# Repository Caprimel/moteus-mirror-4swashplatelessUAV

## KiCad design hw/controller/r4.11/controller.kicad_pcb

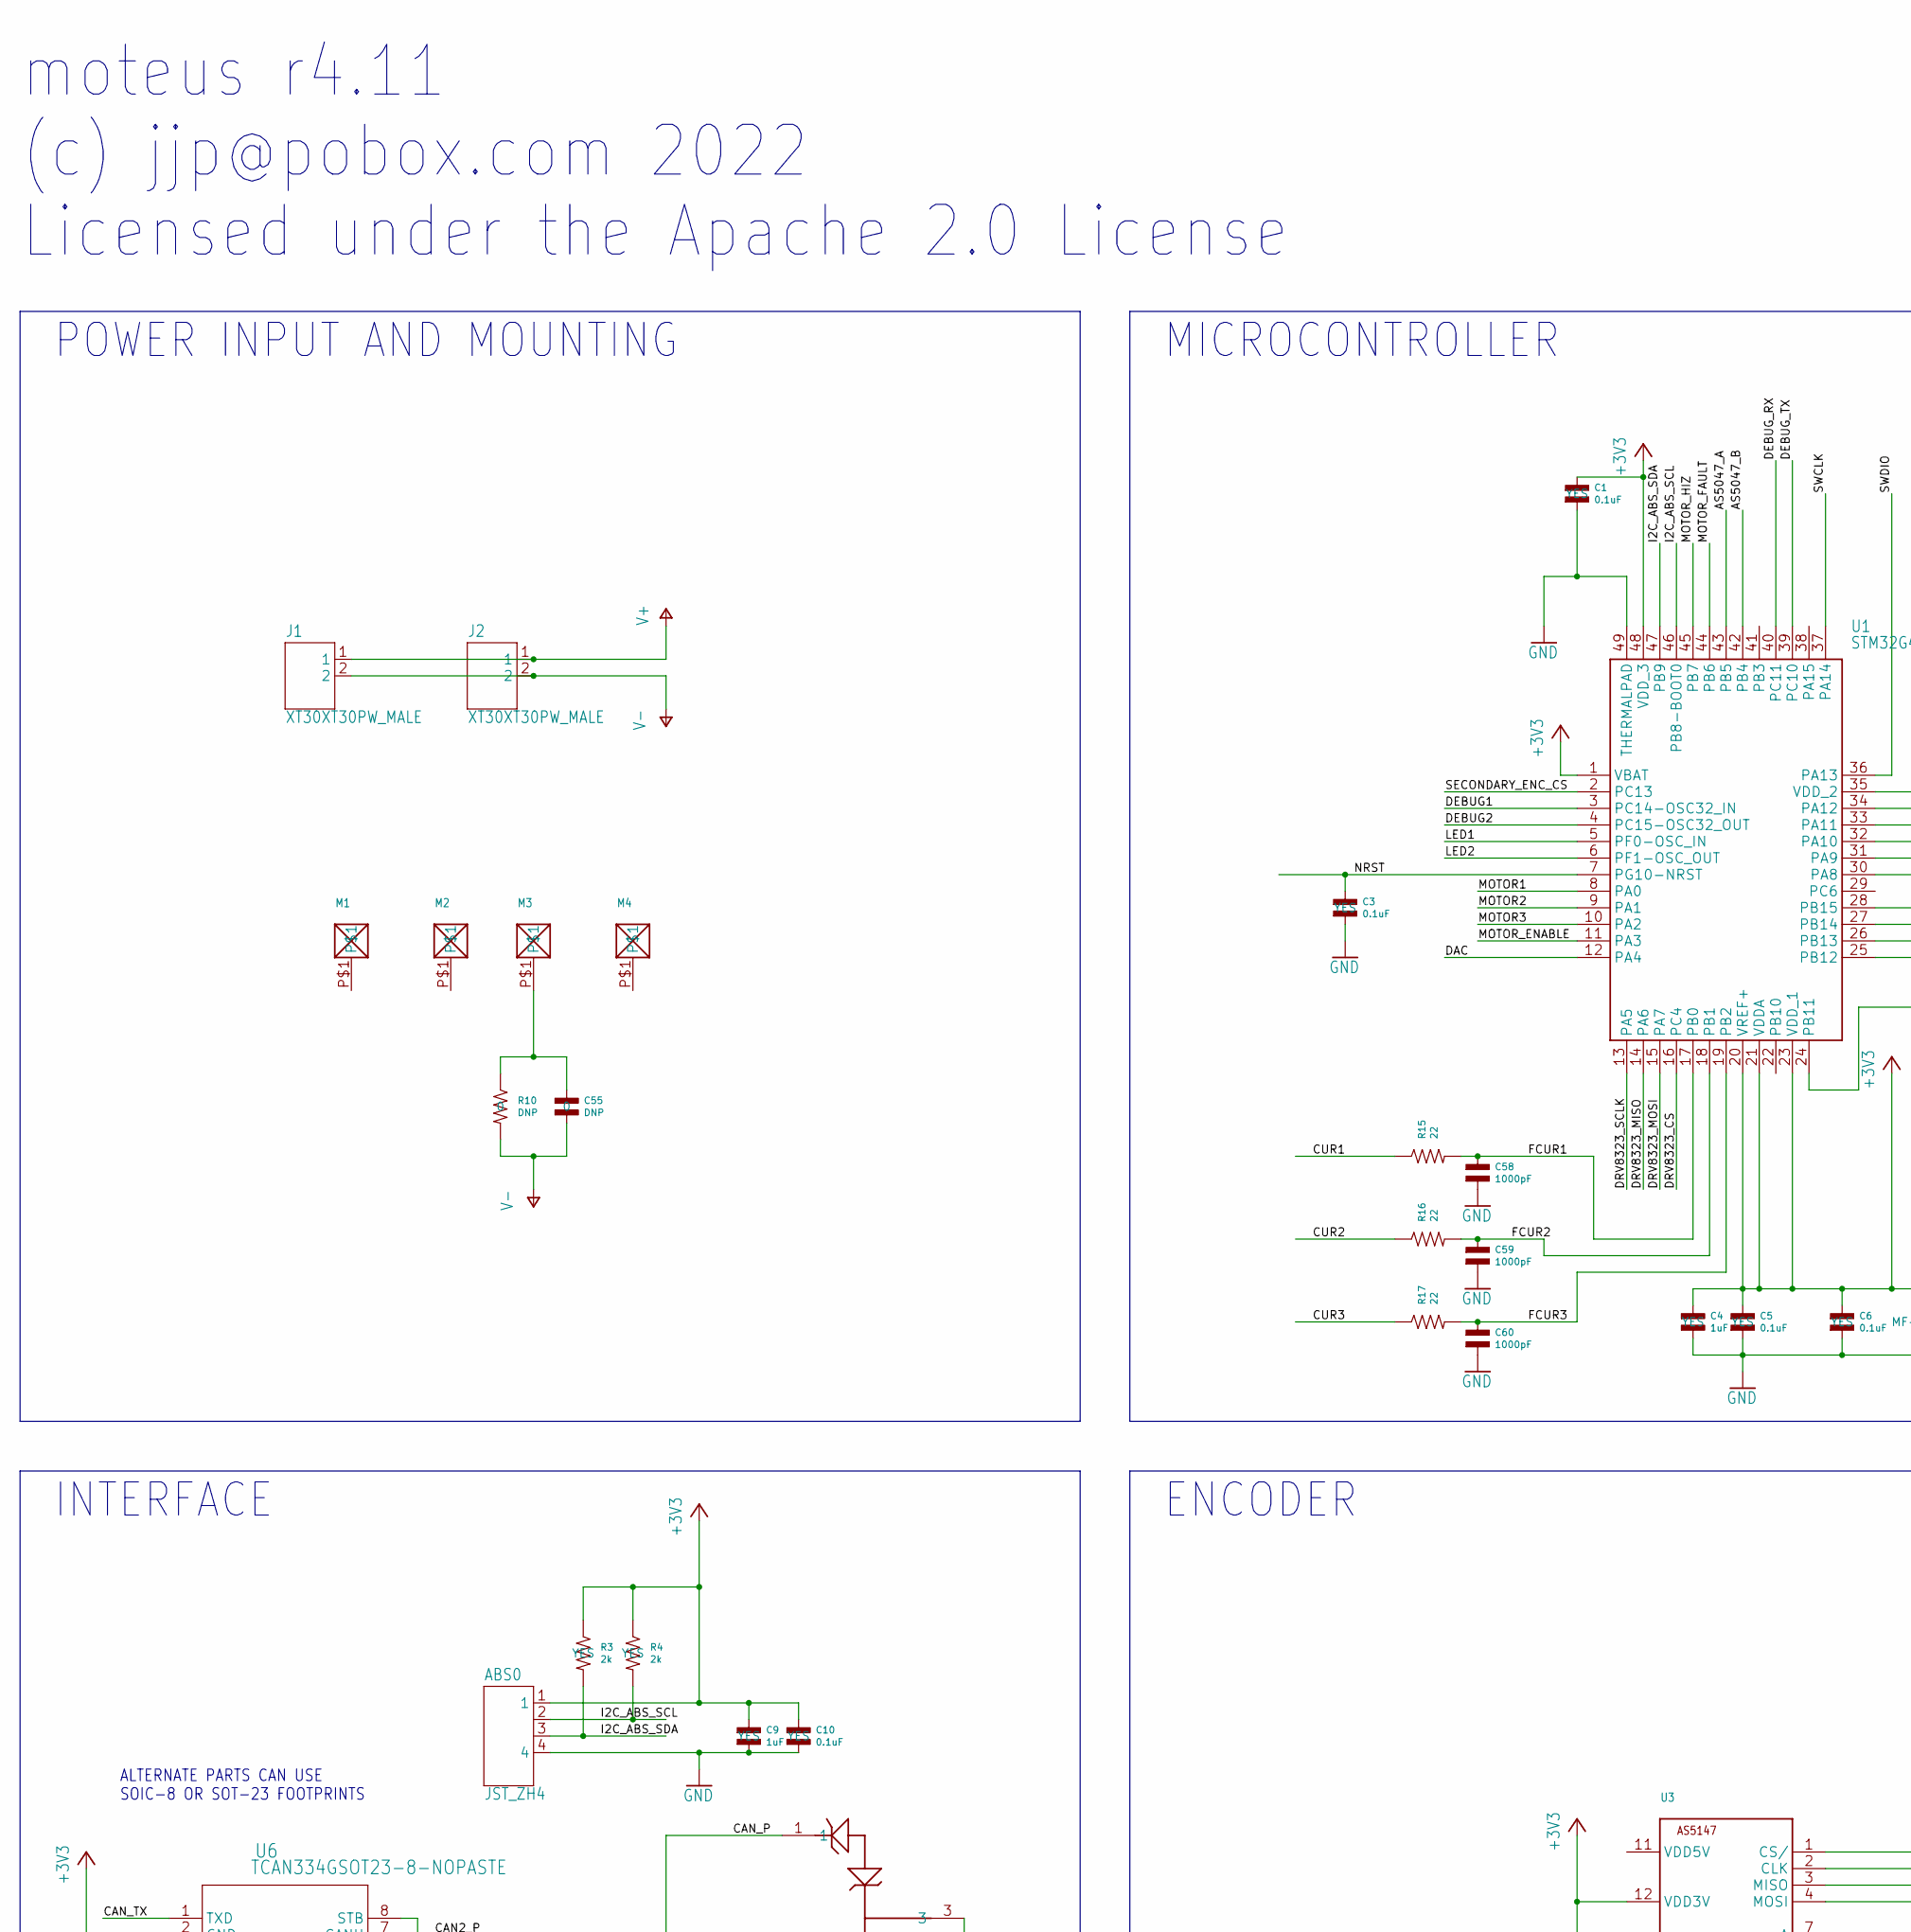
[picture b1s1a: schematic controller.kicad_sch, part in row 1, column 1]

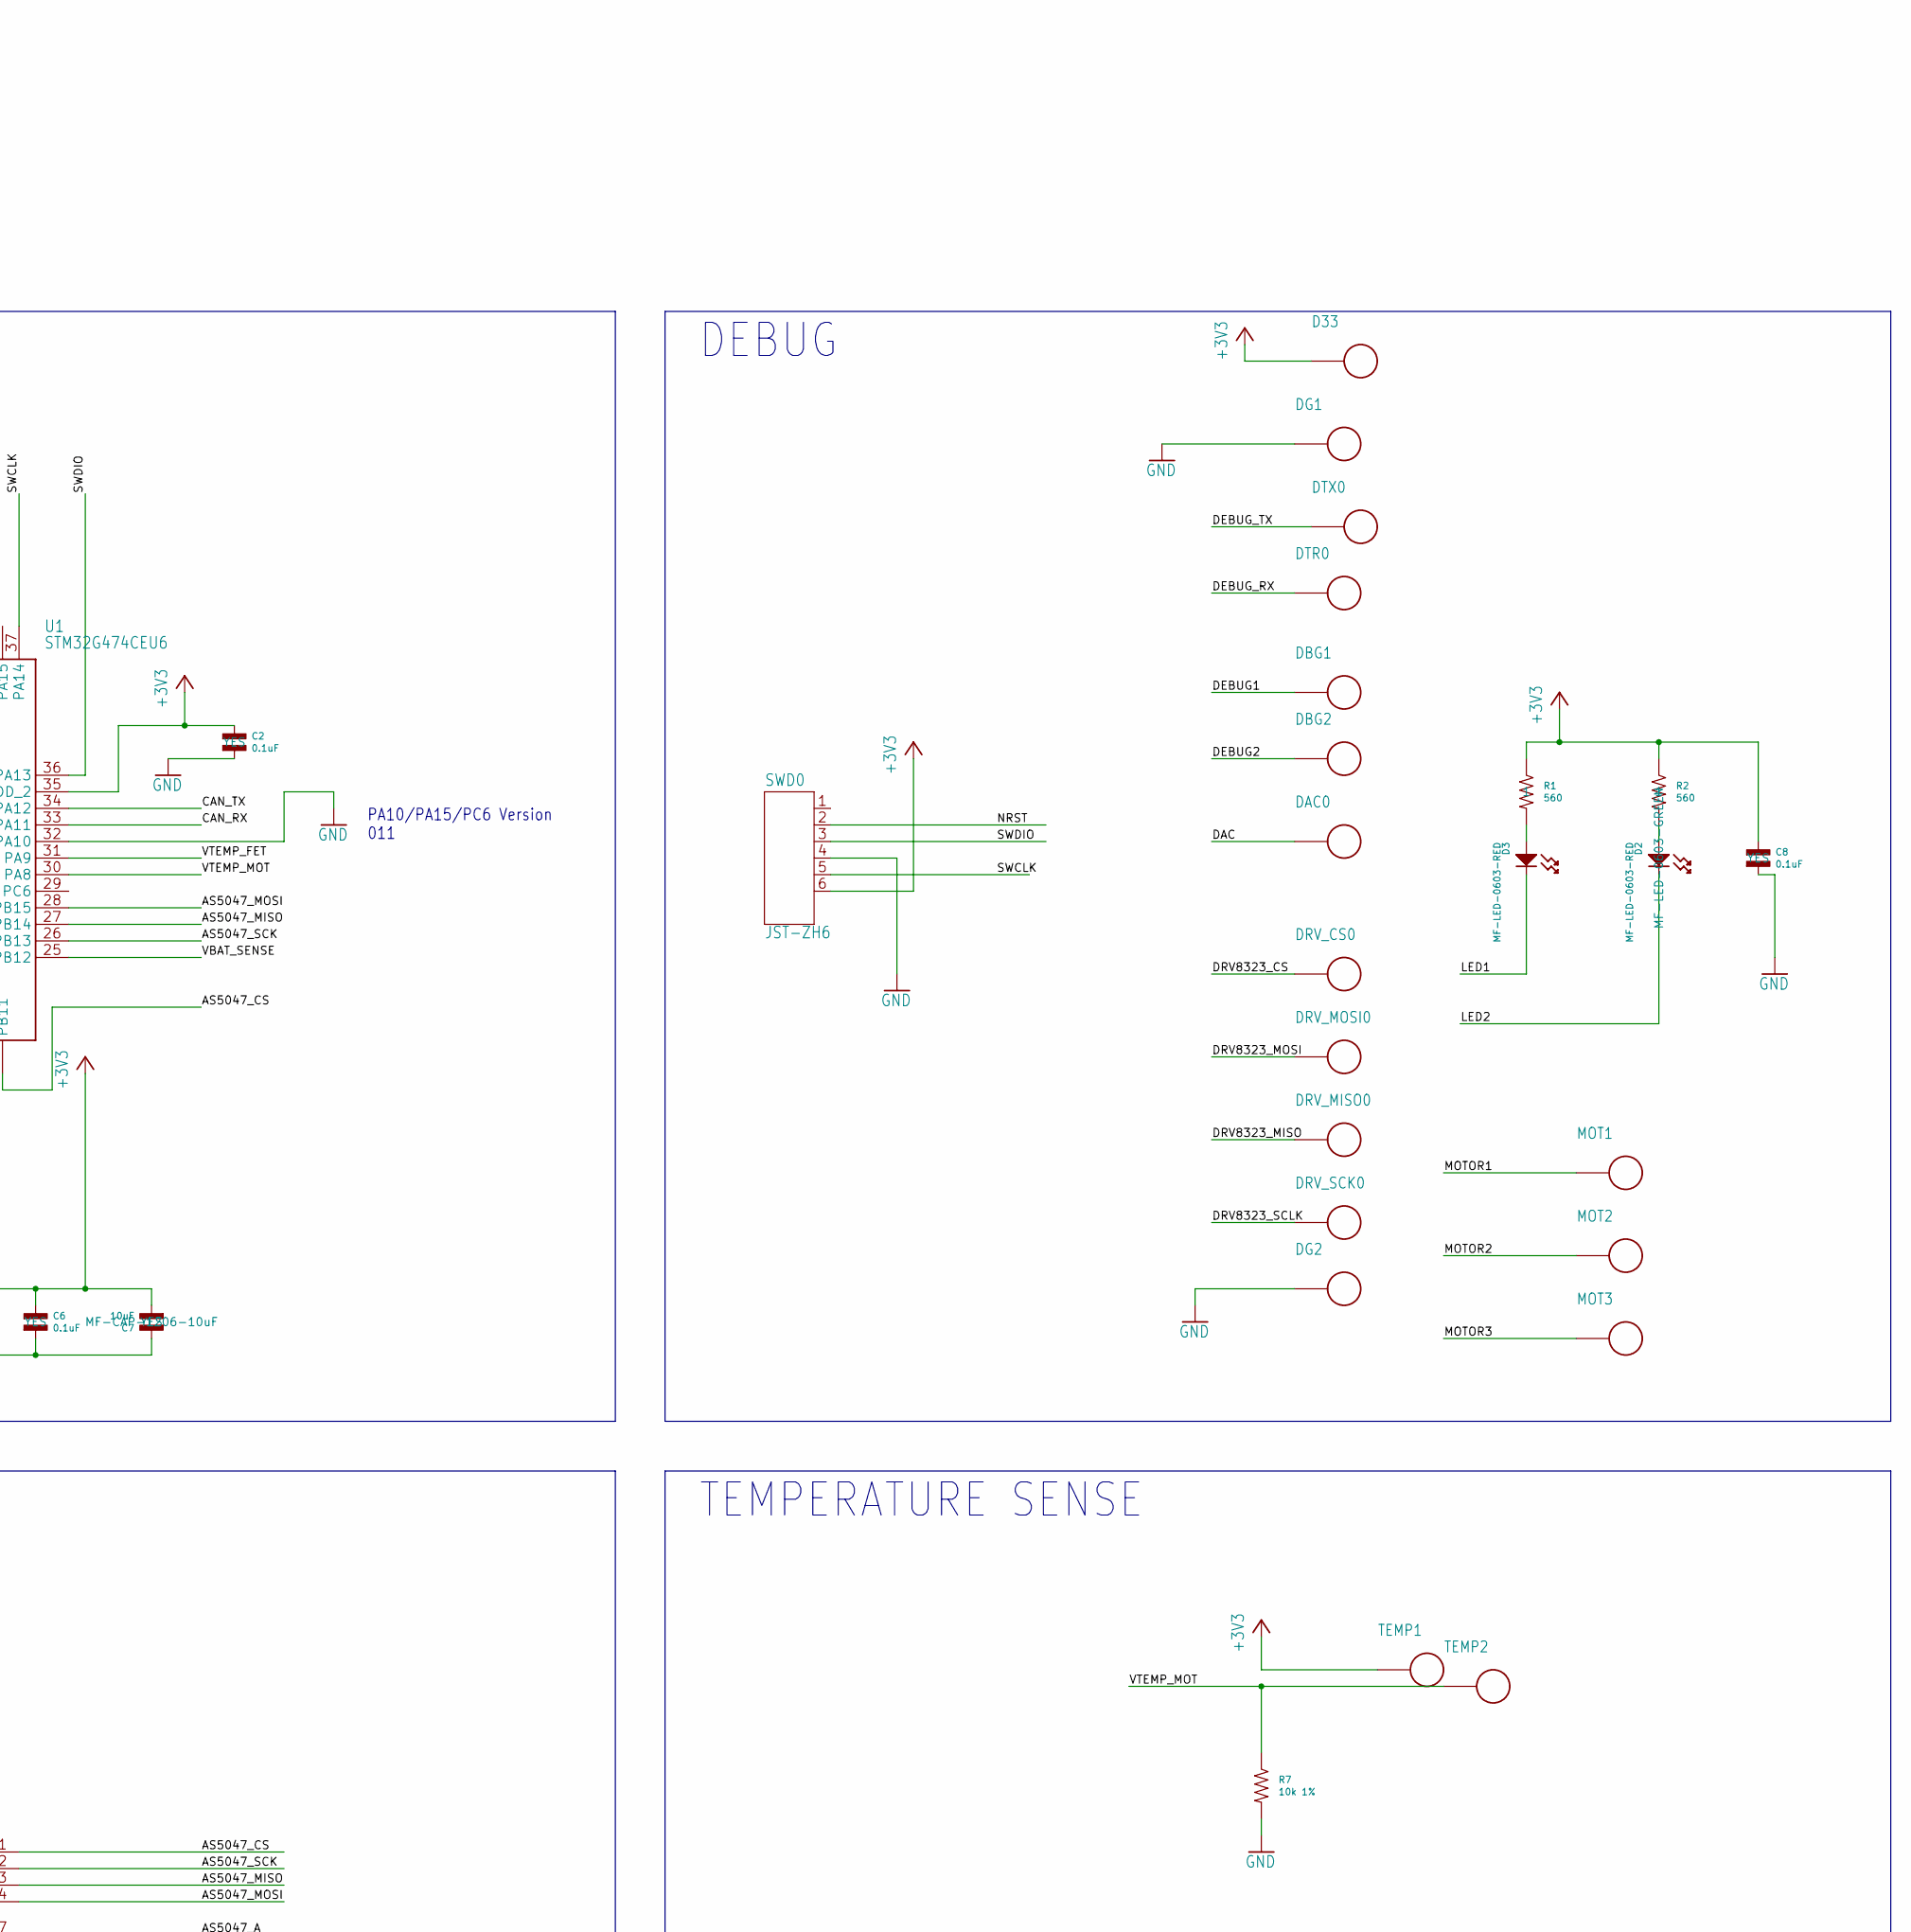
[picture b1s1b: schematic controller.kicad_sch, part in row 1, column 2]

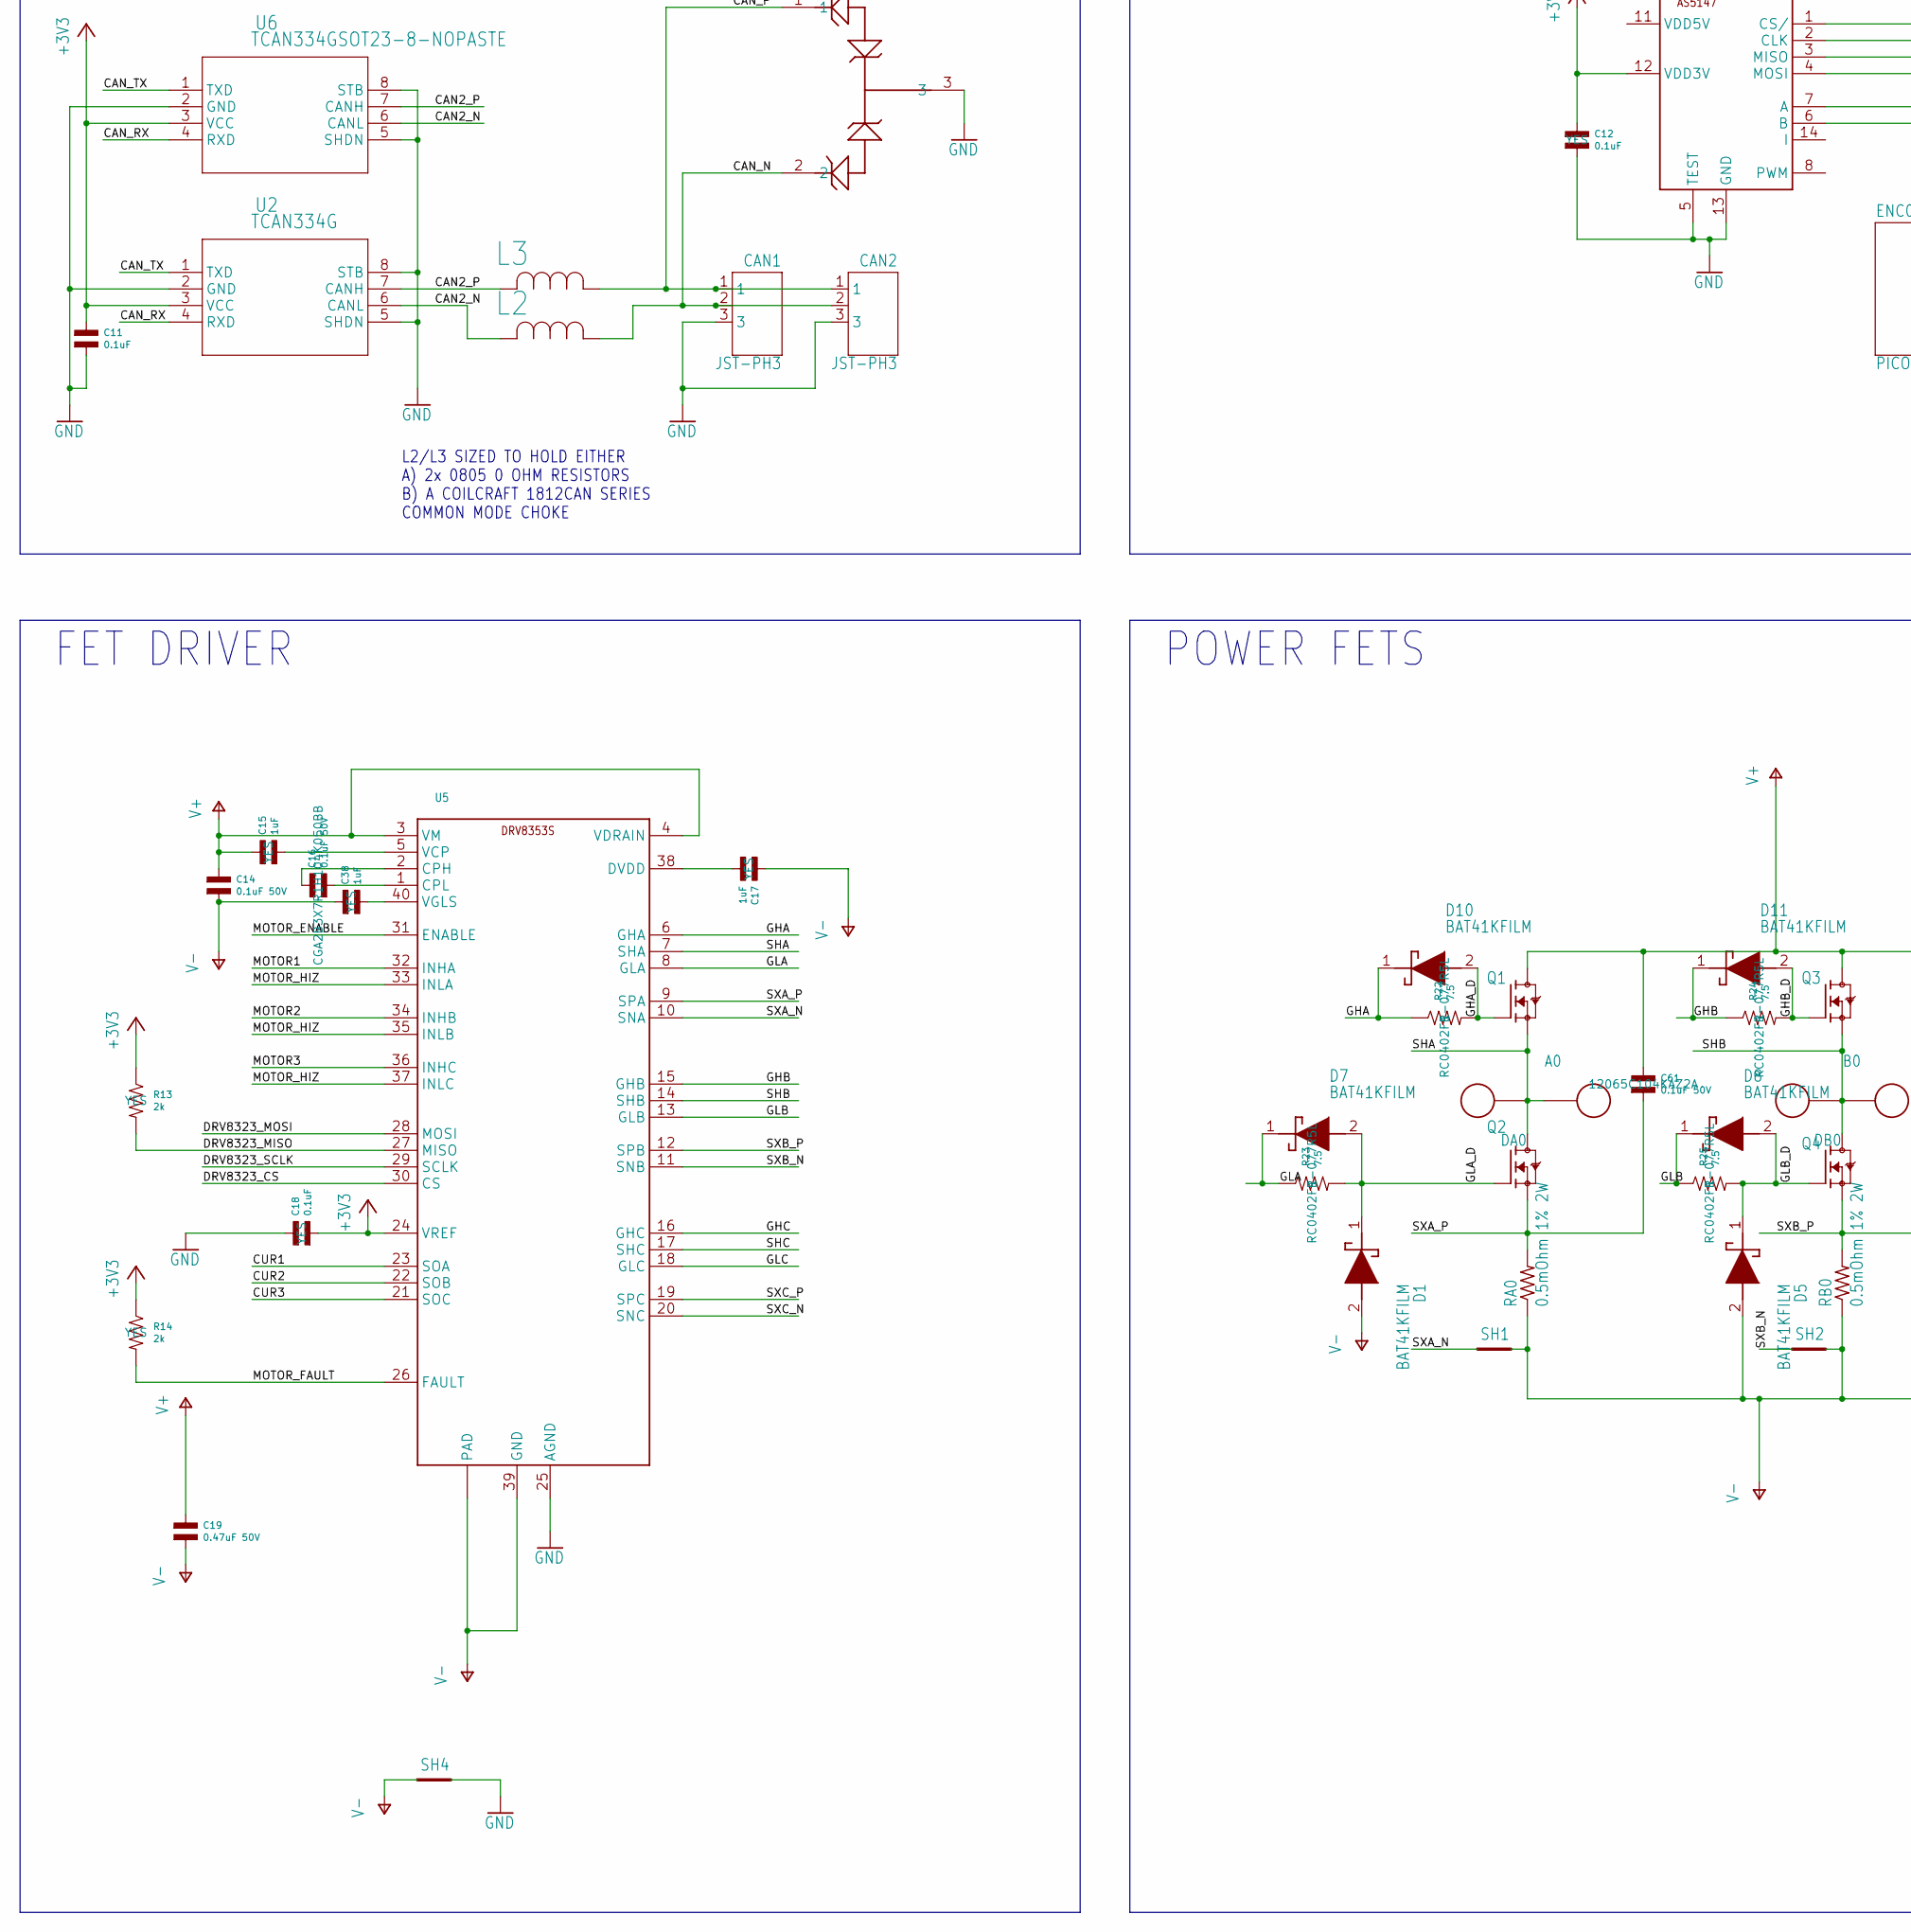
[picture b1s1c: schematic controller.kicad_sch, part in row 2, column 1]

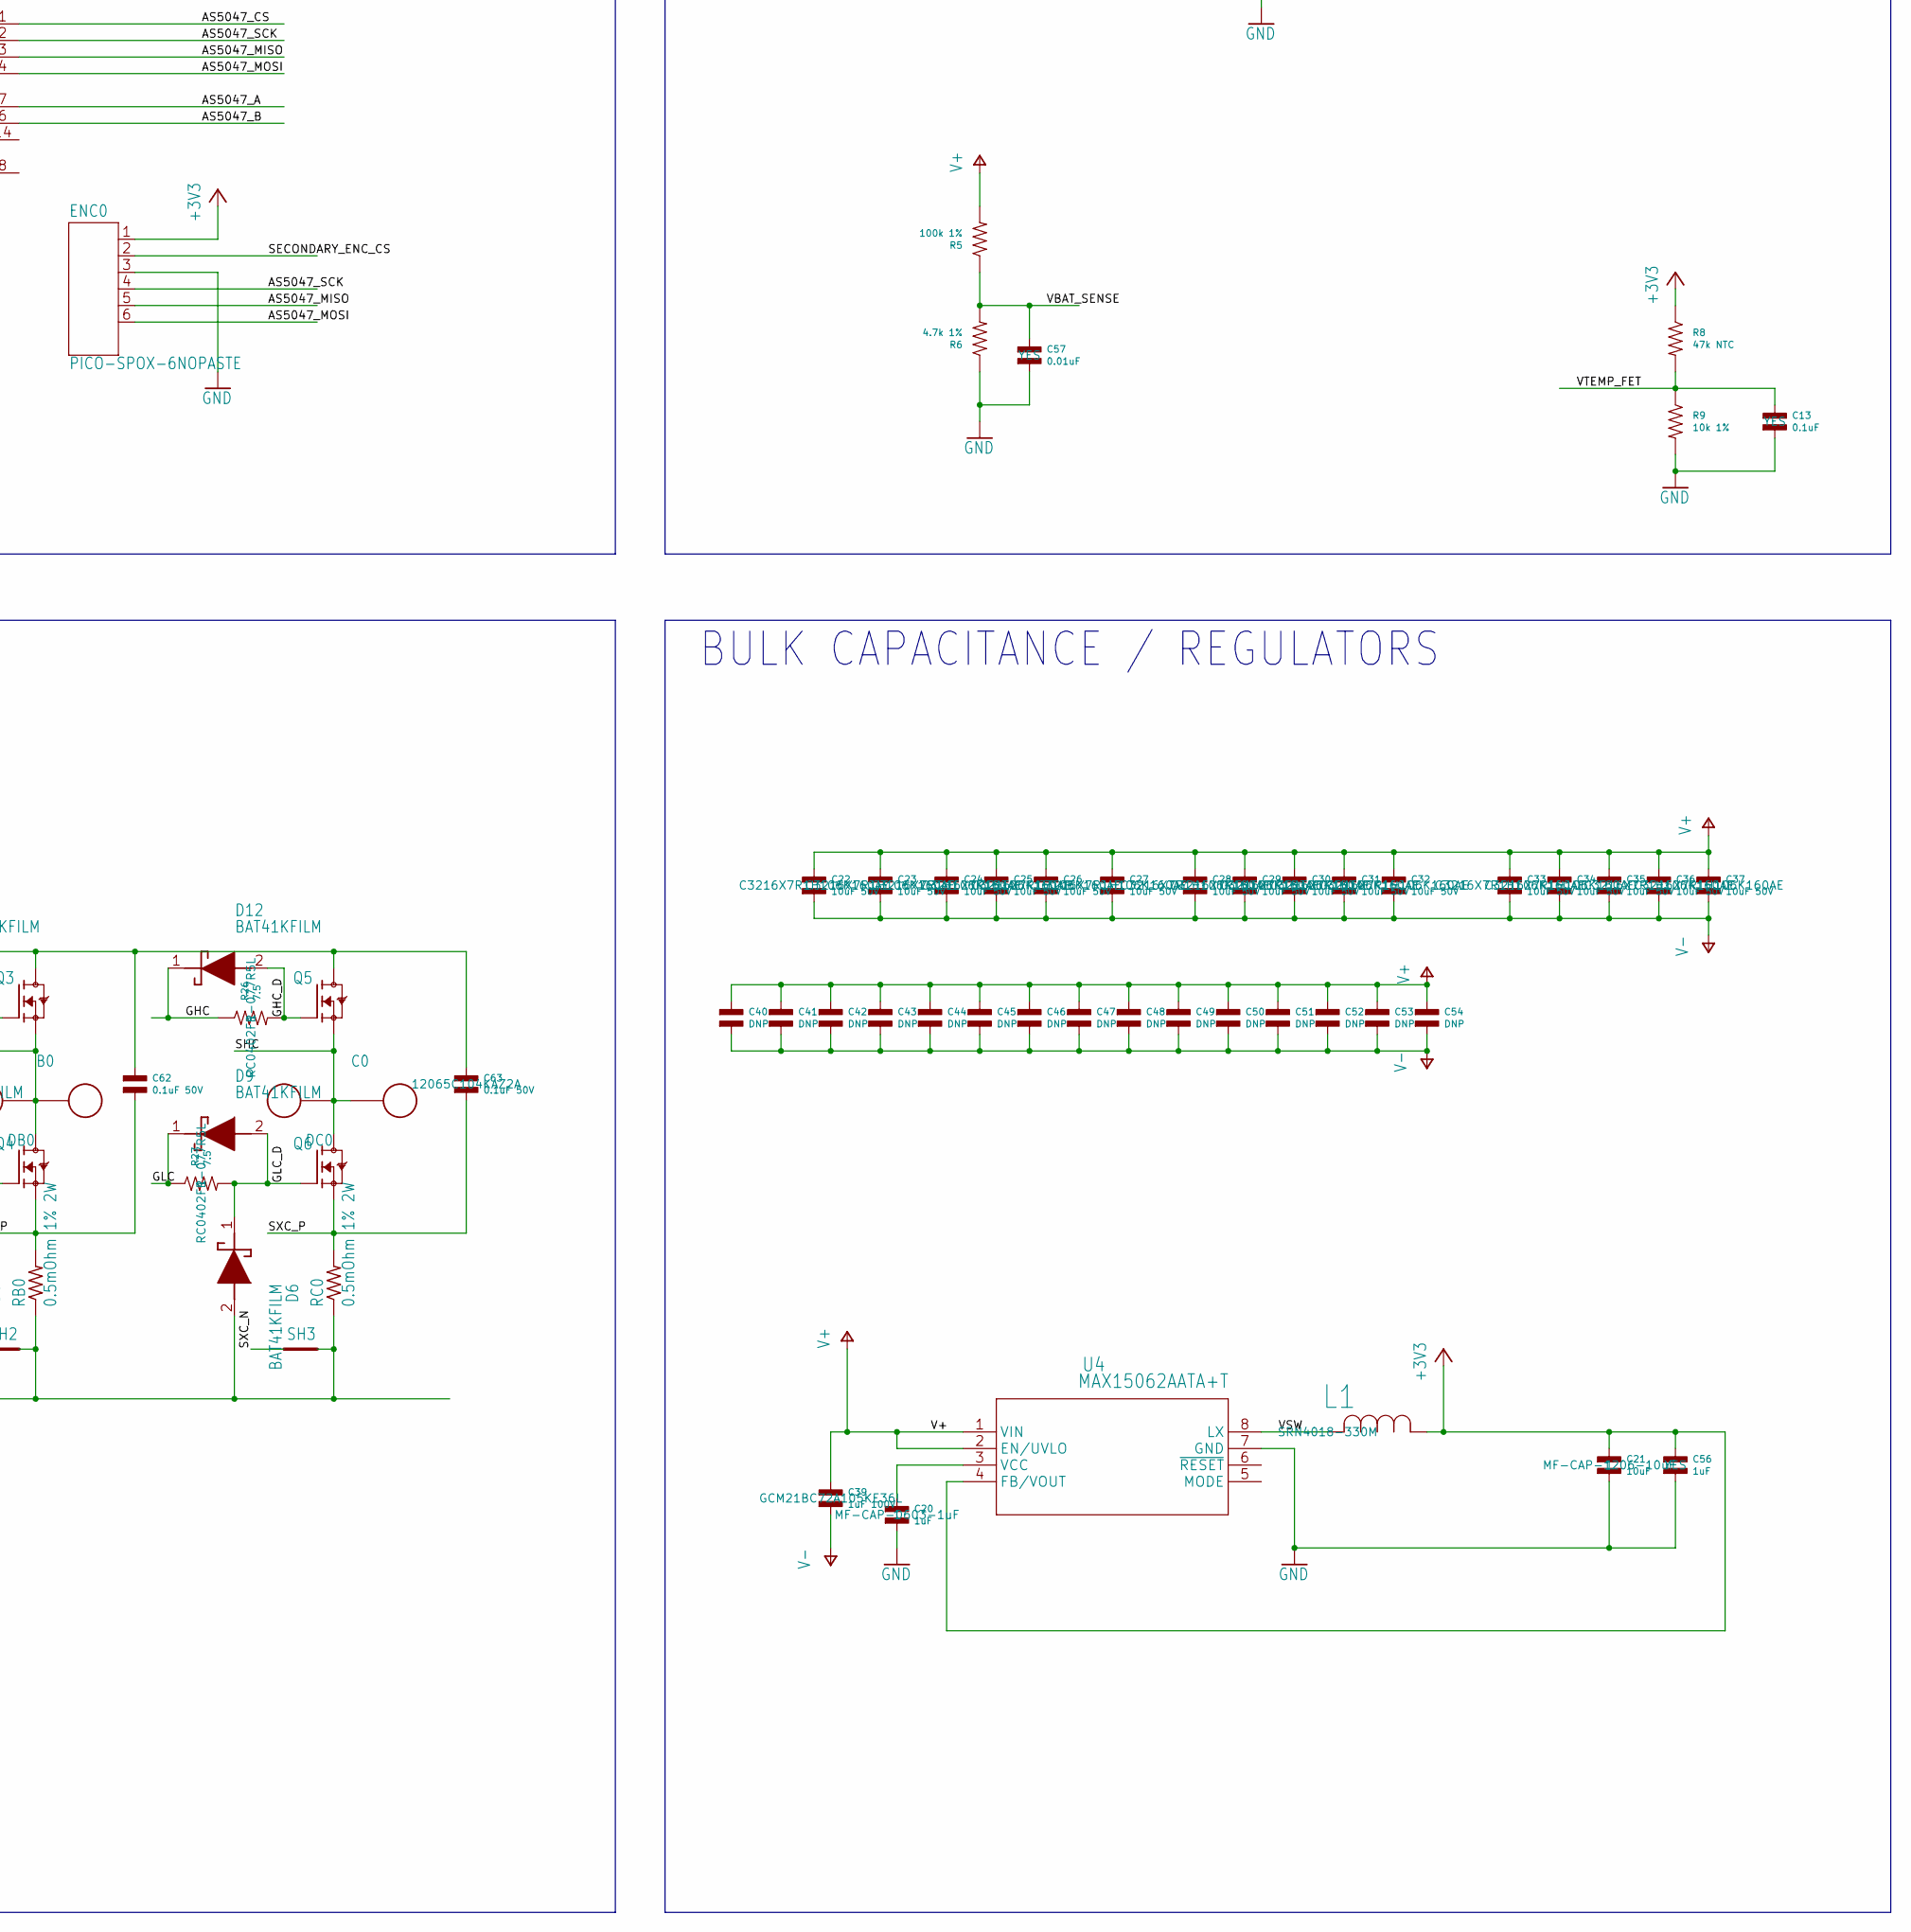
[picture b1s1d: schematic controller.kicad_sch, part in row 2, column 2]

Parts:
A0: PAD16AWG_PAD; 16AWG_PAD
ABS0: JST_ZH4; JST_S4B-ZR-SM4A-TF(LF)(SN); MPN S4B-ZR-SM4A-TF(LF)(SN)
B0: PAD16AWG_PAD; 16AWG_PAD
C0: PAD16AWG_PAD; 16AWG_PAD
C1, C2, C3, C5, C6, C8, C10, C12, C13, C18: 0.1uF; C0402; MPN MF-CAP-0402-0.1uF
C4, C9, C15, C17, C56: 1uF; C0402; MPN MF-CAP-0402-1uF
C7, C21: 10uF; C1206; MPN MF-CAP-1206-10uF
C11: 0.1uF; C0402_NOBORDER; MPN MF-CAP-0402-0.1uF
C14, C16: 0.1uF 50V; C0402; MPN CGA2B3X7R1H104K050BB
C19: 0.47uF 50V; C0402; MPN GRM155R61H474KE11D
C20: 1uF; C0603; MPN MF-CAP-0603-1uF
C22, C23, C24, C25, C26, C27, C28, C29, C30, C31, C32, C33, C34, C36, C37: 10uF 50V; C1206; MPN C3216X7R1H106K160AE
C35: 10uF 50V; C1206_NOBORDER; MPN C3216X7R1H106K160AE
C38: 1uF; C0603; MPN C1608X7R1E105K080AE
C39: 1uF 100V; C0805; MPN GCM21BC72A105KE36L
C40, C41, C42, C43, C44, C45, C46, C47, C48, C49, C50, C51, C52, C53, C54: DNP; C1206_NOCREAM
C55: DNP; C0402
C57: 0.01uF; C0402; MPN MF-CAP-0402-0.01uF
C58, C59, C60: 1000pF; C0402_NOBORDER; MPN MF-CAP-0402-1nF
C61, C63: 0.1uF 50V; C1206; MPN 12065C104KAZ2A
C62: 0.1uF 50V; C0603_NOBORDER; MPN 06035C104KAZ2A
CAN1, CAN2: JST-PH3; JST_S3B-PH-SM4-TB(LF)(SN); MPN S3B-PH-SM4-TB(LF)(SN)
D1, D5, D6, D7, D8, D9, D10, D11, D12: BAT41KFILM; SODFL1608X70N; MPN BAT41KFILM
D2: MF-LED-0603-RED; LED0603; MPN MF-LED-0603-GREEN
D3: MF-LED-0603-RED; LED0603
D4: DUAL_TVS; SOT23-3; MPN CDSOT23-0502B
D33: PAD24AWG_PAD; 24AWG_PAD
DA0: PAD24AWG_PAD; 24AWG_PAD
DAC0: PAD24AWG_PAD; 24AWG_PAD
DB0: PAD24AWG_PAD; 24AWG_PAD
DBG1, DBG2: PAD24AWG_PAD; 24AWG_PAD
DC0: PAD24AWG_PAD; 24AWG_PAD
DG1, DG2: PAD24AWG_PAD; 24AWG_PAD
DRV_CS0: PAD24AWG_PAD; 24AWG_PAD
DRV_MISO0: PAD24AWG_PAD; 24AWG_PAD
DRV_MOSI0: PAD24AWG_PAD; 24AWG_PAD
DRV_SCK0: PAD24AWG_PAD; 24AWG_PAD
DTR0: PAD24AWG_PAD; 24AWG_PAD
DTX0: PAD24AWG_PAD; 24AWG_PAD
ENC0: PICO-SPOX-6NOPASTE; PICO-SPOX-SMT-RA-6-NOPASTE
J1, J2: XT30XT30PW_MALE; XT30PW_MALE
L1: SRN4018-220M; IND_BOURNS_SRN4018; MANUFACTURER_PART_NUMBER SRN4018-330M
L2, L3: HALF_CHOKE; 1812_COMMON_HALF; MPN MF-RES-0805-0
M1, M2, M3, M4: MOUNT; M2.5MOUNT
MOT1, MOT2, MOT3: PAD24AWG_PAD; 24AWG_PAD
Q1, Q2, Q3, Q4, Q5, Q6: TPH1R204PLSOP_ADVANCE_8; SOP_ADVANCE_8; MPN TPH2R506PL,L1Q
R1, R2: 560; R0402; MPN MF-RES-0402-560
R3, R4, R13, R14: 2k; R0402; MPN MF-RES-0402-2K
R5: 100k 1%; R0402; MPN RC0402FR-07100KL
R6: 4.7k 1%; R0402; MPN RC0402FR-074K7L
R7, R9: 10k 1%; R0402; MPN RC0402FR-0710KL
R8: 47k NTC; R0402; MPN NCP15WB473F03RC
R10: DNP; R0402
R15, R16, R17: 22; R0402_NOBORDER; MPN MF-RES-0402-22
R22, R23, R24, R25, R26, R27: 7.5; R0402; MPN RC0402FR-077R5L
RA0: 0.5mOhm 1% 2W; M1206; MPN HCS1206FTL500
RB0: 0.5mOhm 1% 2W; M1206; MPN HCS1206FTL500
RC0: 0.5mOhm 1% 2W; M1206; MPN HCS1206FTL500
SH1, SH2, SH3: SHORTT5; SHORT_TOP-50
SH4: SHORTMEDIUM; SHORT_TOP-MEDIUM
SWD0: JST-ZH6; JST_S6B-ZR-SM4A-TF(LF)(SN); MPN S6B-ZR-SM4A-TF(LF)(SN)
TEMP1, TEMP2: PAD24AWG_PAD; 24AWG_PAD
U1: STM32G474CEU6; QFN50P700X700X60-49N; MPN STM32G474CEU6
U2: TCAN334G; SOIC8; MPN TCAN337GDR
U3: AS5147; TSSOP14; MPN AS5047P-ATSM
U4: MAX15062AATA+T; 21-0487A_MXM; MPN MAX15062AATA+T
U5: DRV8353S; WQFN-40; MPN DRV8353FSRTAR
U6: TCAN334GSOT23-8-NOPASTE; SOT23-8-NOPASTE; MPN TCAN334GDCNT

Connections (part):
+3V3: ABS0.1, C1.P$1, C2.P$1, C4.P$1, C5.P$1, C6.P$1, C7.P$2, C8.P$1, C9.P$1, C10.P$1, C11.P$1, C12.P$1, C18.P$2, C21.P$1, C56.P$1, D33.P$1, ENC0.1, L1.1, R1.P$1, R2.P$1, R3.P$1, R4.P$1, R8.P$1, R13.P$1, R14.P$1, SWD0.6, TEMP1.P$1, U1.1 (VBAT), U1.20 (VREF+), U1.21 (VDDA), U1.23 (VDD_1), U1.35 (VDD_2), U1.48 (VDD_3), U2.3 (VCC), U3.12 (VDD3V), U4.4 (FB/VOUT), U5.24 (VREF), U6.3 (VCC)
AS5047_A: U1.43 (PB5), U3.7 (A)
AS5047_B: U1.42 (PB4), U3.6 (B)
AS5047_CS: U1.24 (PB11), U3.1 (CS/)
AS5047_MISO: ENC0.5, U1.27 (PB14), U3.3 (MISO)
AS5047_MOSI: ENC0.6, U1.28 (PB15), U3.4 (MOSI)
AS5047_SCK: ENC0.4, U1.26 (PB13), U3.2 (CLK)
CAN2_N: L2.P$2 (2), U2.6 (CANL), U6.6 (CANL)
CAN2_P: L3.P$2 (2), U2.7 (CANH), U6.7 (CANH)
CAN_N: CAN1.2, CAN2.2, D4.2, L2.P$1 (1)
CAN_P: CAN1.1, CAN2.1, D4.1, L3.P$1 (1)
CAN_RX: U1.33 (PA11), U2.4 (RXD), U6.4 (RXD)
CAN_TX: U1.34 (PA12), U2.1 (TXD), U6.1 (TXD)
CUR1: R15.P$1, U5.23 (SOA)
CUR2: R16.P$1, U5.22 (SOB)
CUR3: R17.P$1, U5.21 (SOC)
DAC: DAC0.P$1, U1.12 (PA4)
DEBUG1: DBG1.P$1, U1.3 (PC14-OSC32_IN)
DEBUG2: DBG2.P$1, U1.4 (PC15-OSC32_OUT)
DEBUG_RX: DTR0.P$1, U1.40 (PC11)
DEBUG_TX: DTX0.P$1, U1.39 (PC10)
DRV8323_CS: DRV_CS0.P$1, U1.16 (PC4), U5.30 (CS)
DRV8323_MISO: DRV_MISO0.P$1, R13.P$2, U1.14 (PA6), U5.27 (MISO)
DRV8323_MOSI: DRV_MOSI0.P$1, U1.15 (PA7), U5.28 (MOSI)
DRV8323_SCLK: DRV_SCK0.P$1, U1.13 (PA5), U5.29 (SCLK)
FCUR1: C58.P$1, R15.P$2, U1.17 (PB0)
FCUR2: C59.P$1, R16.P$2, U1.18 (PB1)
FCUR3: C60.P$1, R17.P$2, U1.19 (PB2)
GHA: D10.1 (K), R22.P$1, U5.6 (GHA)
GHA_D: D10.2 (A), Q1.4 (G), R22.P$2
GHB: D11.1 (K), R24.P$1, U5.15 (GHB)
GHB_D: D11.2 (A), Q3.4 (G), R24.P$2
GHC: D12.1 (K), R26.P$1, U5.16 (GHC)
GHC_D: D12.2 (A), Q5.4 (G), R26.P$2
GLA: D7.1 (K), R23.P$1, U5.8 (GLA)
GLA_D: D1.1 (K), D7.2 (A), Q2.4 (G), R23.P$2
GLB: D8.1 (K), R25.P$1, U5.13 (GLB)
GLB_D: D5.1 (K), D8.2 (A), Q4.4 (G), R25.P$2
GLC: D9.1 (K), R27.P$1, U5.18 (GLC)
GLC_D: D6.1 (K), D9.2 (A), Q6.4 (G), R27.P$2
GND: ABS0.4, C1.P$2, C2.P$2, C3.P$2, C4.P$2, C5.P$2, C6.P$2, C7.P$1, C8.P$2, C9.P$2, C10.P$2, C11.P$2, C12.P$2, C13.P$2, C18.P$1, C20.P$2, C21.P$2, C56.P$2, C57.P$2, C58.P$2, C59.P$2, C60.P$2, CAN1.3, CAN2.3, D4.3, DG1.P$1, DG2.P$1, ENC0.3, R6.P$1, R7.P$2, R9.P$2, SH4.2, SWD0.4, U1.32 (PA10), U1.49 (THERMALPAD), U2.2 (GND), U2.5 (SHDN), U2.8 (STB), U3.5 (TEST), U3.13 (GND), U4.7 (GND), U5.25 (AGND), U6.2 (GND), U6.5 (SHDN), U6.8 (STB)
I2C_ABS_SCL: ABS0.2, R4.P$2, U1.46 (PB8-BOOT0)
I2C_ABS_SDA: ABS0.3, R3.P$2, U1.47 (PB9)
LED1: D3.CATHODE, U1.5 (PF0-OSC_IN)
LED2: D2.CATHODE, U1.6 (PF1-OSC_OUT)
MOTOR1: MOT1.P$1, U1.8 (PA0), U5.32 (INHA)
MOTOR2: MOT2.P$1, U1.9 (PA1), U5.34 (INHB)
MOTOR3: MOT3.P$1, U1.10 (PA2), U5.36 (INHC)
MOTOR_ENABLE: U1.11 (PA3), U5.31 (ENABLE)
MOTOR_FAULT: R14.P$2, U1.44 (PB6), U5.26 (FAULT)
MOTOR_HIZ: U1.45 (PB7), U5.33 (INLA), U5.35 (INLB), U5.37 (INLC)
unnamed: C55.P$1, M3.P$1, R10.P$1
unnamed: C38.P$2, U5.40 (VGLS)
unnamed: C20.P$1, U4.3 (VCC)
unnamed: C16.P$2, U5.1 (CPL)
unnamed: C16.P$1, U5.2 (CPH)
unnamed: C15.P$2, U5.5 (VCP)
unnamed: C17.P$2, U5.38 (DVDD)
unnamed: D3.ANODE, R1.P$2
unnamed: D2.ANODE, R2.P$2
NRST: C3.P$1, SWD0.2, U1.7 (PG10-NRST)
SECONDARY_ENC_CS: ENC0.2, U1.2 (PC13)
SHA: A0.1, DA0.P$1, Q1.1 (S), Q1.2 (S), Q1.3 (S), Q2.5 (D), Q2.6 (D), Q2.7 (D), Q2.8 (D), Q2.PAD (D), U5.7 (SHA)
SHB: B0.1, DB0.P$1, Q3.1 (S), Q3.2 (S), Q3.3 (S), Q4.5 (D), Q4.6 (D), Q4.7 (D), Q4.8 (D), Q4.PAD (D), U5.14 (SHB)
SHC: C0.1, DC0.P$1, Q5.1 (S), Q5.2 (S), Q5.3 (S), Q6.5 (D), Q6.6 (D), Q6.7 (D), Q6.8 (D), Q6.PAD (D), U5.17 (SHC)
SWCLK: SWD0.5, U1.37 (PA14)
SWDIO: SWD0.3, U1.36 (PA13)
SXA_N: SH1.1, U5.10 (SNA)
SXA_P: C61.P$2, Q2.1 (S), Q2.2 (S), Q2.3 (S), RA0.2, U5.9 (SPA)
SXB_N: SH2.1, U5.11 (SNB)
SXB_P: C62.P$2, Q4.1 (S), Q4.2 (S), Q4.3 (S), RB0.2, U5.12 (SPB)
SXC_N: SH3.1, U5.20 (SNC)
SXC_P: C63.P$2, Q6.1 (S), Q6.2 (S), Q6.3 (S), RC0.2, U5.19 (SPC)
V+: C14.P$1, C15.P$1, C19.P$1, C22.P$1, C23.P$1, C24.P$1, C25.P$1, C26.P$1, C27.P$1, C28.P$1, C29.P$1, C30.P$1, C31.P$1, C32.P$1, C33.P$1, C34.P$1, C35.P$1, C36.P$1, C37.P$1, C39.P$1, C40.P$1, C41.P$1, C42.P$1, C43.P$1, C44.P$1, C45.P$1, C46.P$1, C47.P$1, C48.P$1, C49.P$1, C50.P$1, C51.P$1, C52.P$1, C53.P$1, C54.P$1, C61.P$1, C62.P$1, C63.P$1, J1.1, J2.1, Q1.5 (D), Q1.6 (D), Q1.7 (D), Q1.8 (D), Q1.PAD (D), Q3.5 (D), Q3.6 (D), Q3.7 (D), Q3.8 (D), Q3.PAD (D), Q5.5 (D), Q5.6 (D), Q5.7 (D), Q5.8 (D), Q5.PAD (D), R5.P$2, U4.1 (VIN), U4.2 (EN/UVLO), U5.3 (VM), U5.4 (VDRAIN)
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
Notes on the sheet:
POWER INPUT AND MOUNTING
L2/L3 SIZED TO HOLD EITHER A) 2x 0805 0 OHM RESISTORS B) A COILCRAFT 1812CAN SERIES COMMON MODE CHOKE
POWER FETS
MICROCONTROLLER
FET DRIVER
BULK CAPACITANCE / REGULATORS
DEBUG
ALTERNATE PARTS CAN USE SOIC-8 OR SOT-23 FOOTPRINTS
moteus r4.11 (c) jjp@pobox.com 2022 Licensed under the Apache 2.0 License
PA10/PA15/PC6 Version 011
INTERFACE
TEMPERATURE SENSE
ENCODER

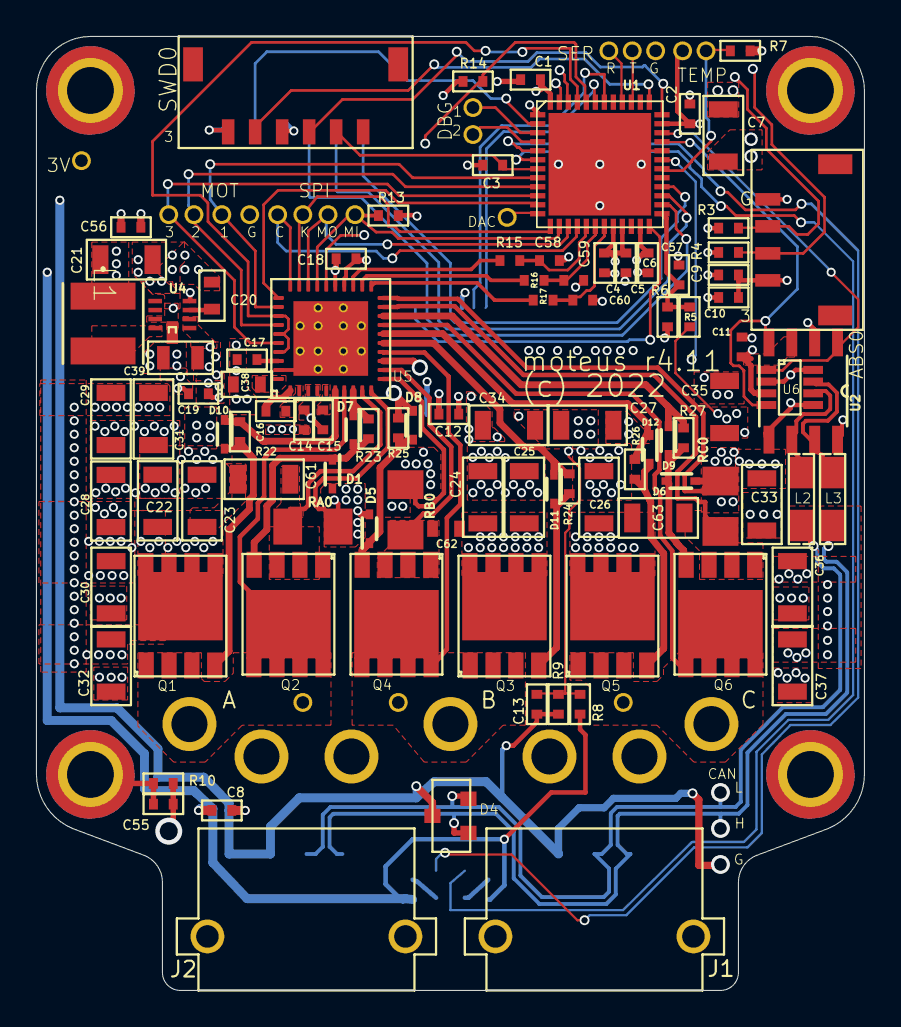
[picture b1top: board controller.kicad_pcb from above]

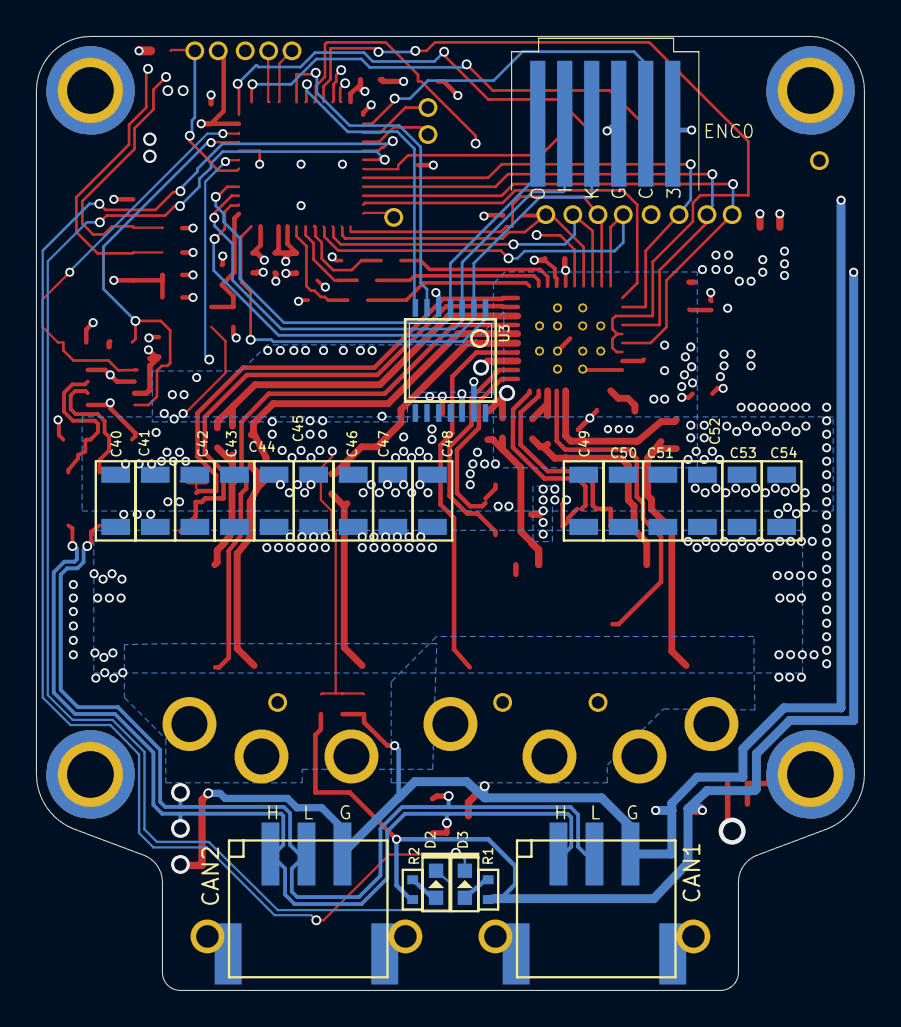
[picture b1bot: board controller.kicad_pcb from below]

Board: 4 copper layers, 46.0 x 53.0 mm, 152 parts (23 on the bottom side), 79 nets.

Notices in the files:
hw/controller/r4.11/controller.kicad_pcb:
(c) 2022
